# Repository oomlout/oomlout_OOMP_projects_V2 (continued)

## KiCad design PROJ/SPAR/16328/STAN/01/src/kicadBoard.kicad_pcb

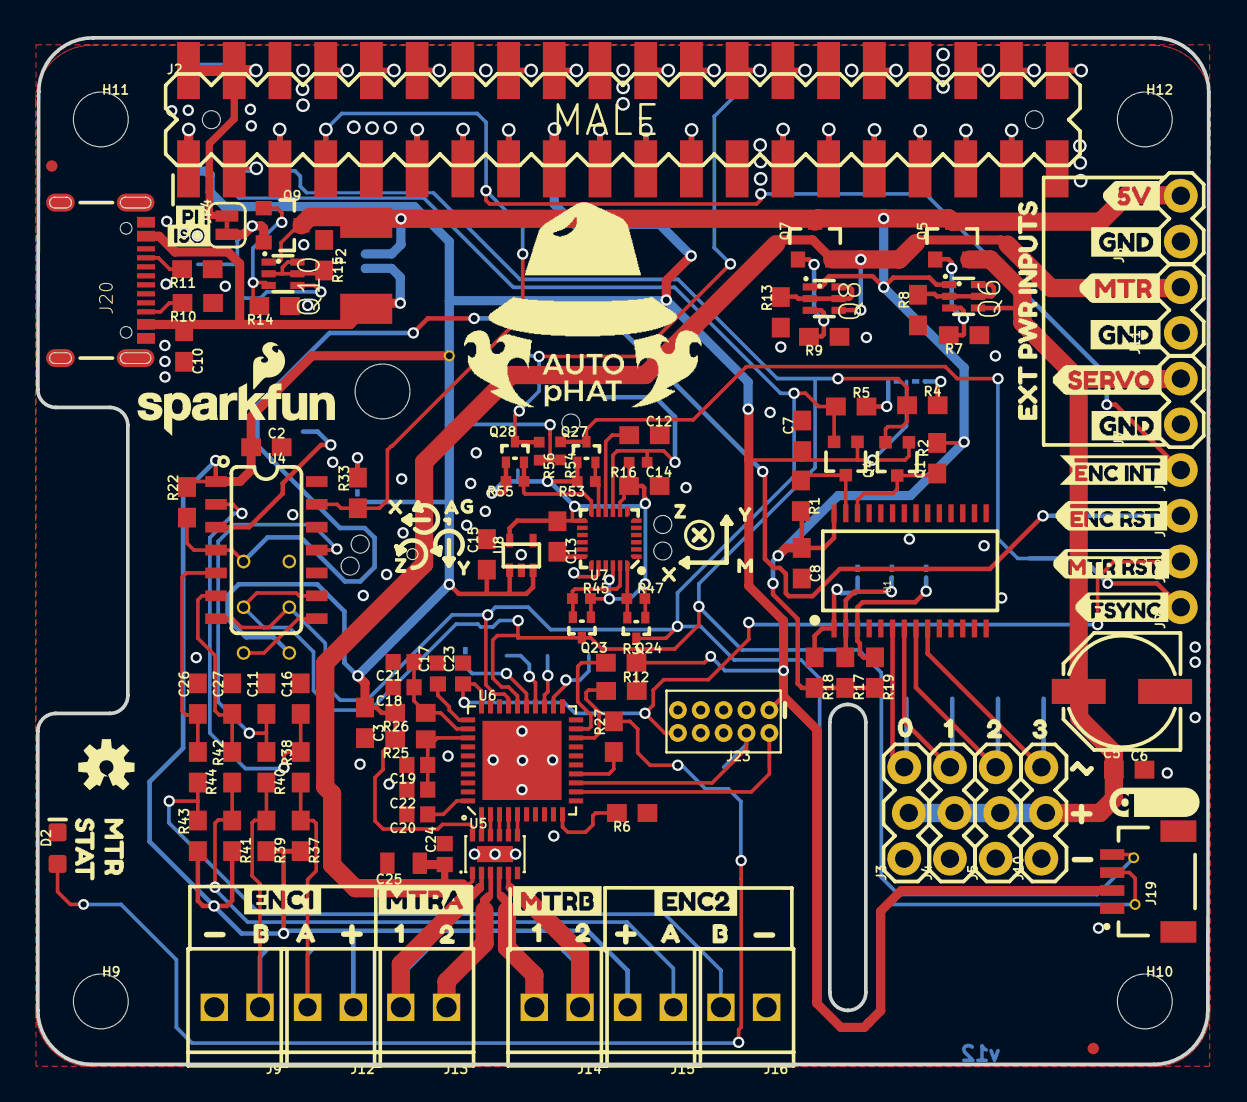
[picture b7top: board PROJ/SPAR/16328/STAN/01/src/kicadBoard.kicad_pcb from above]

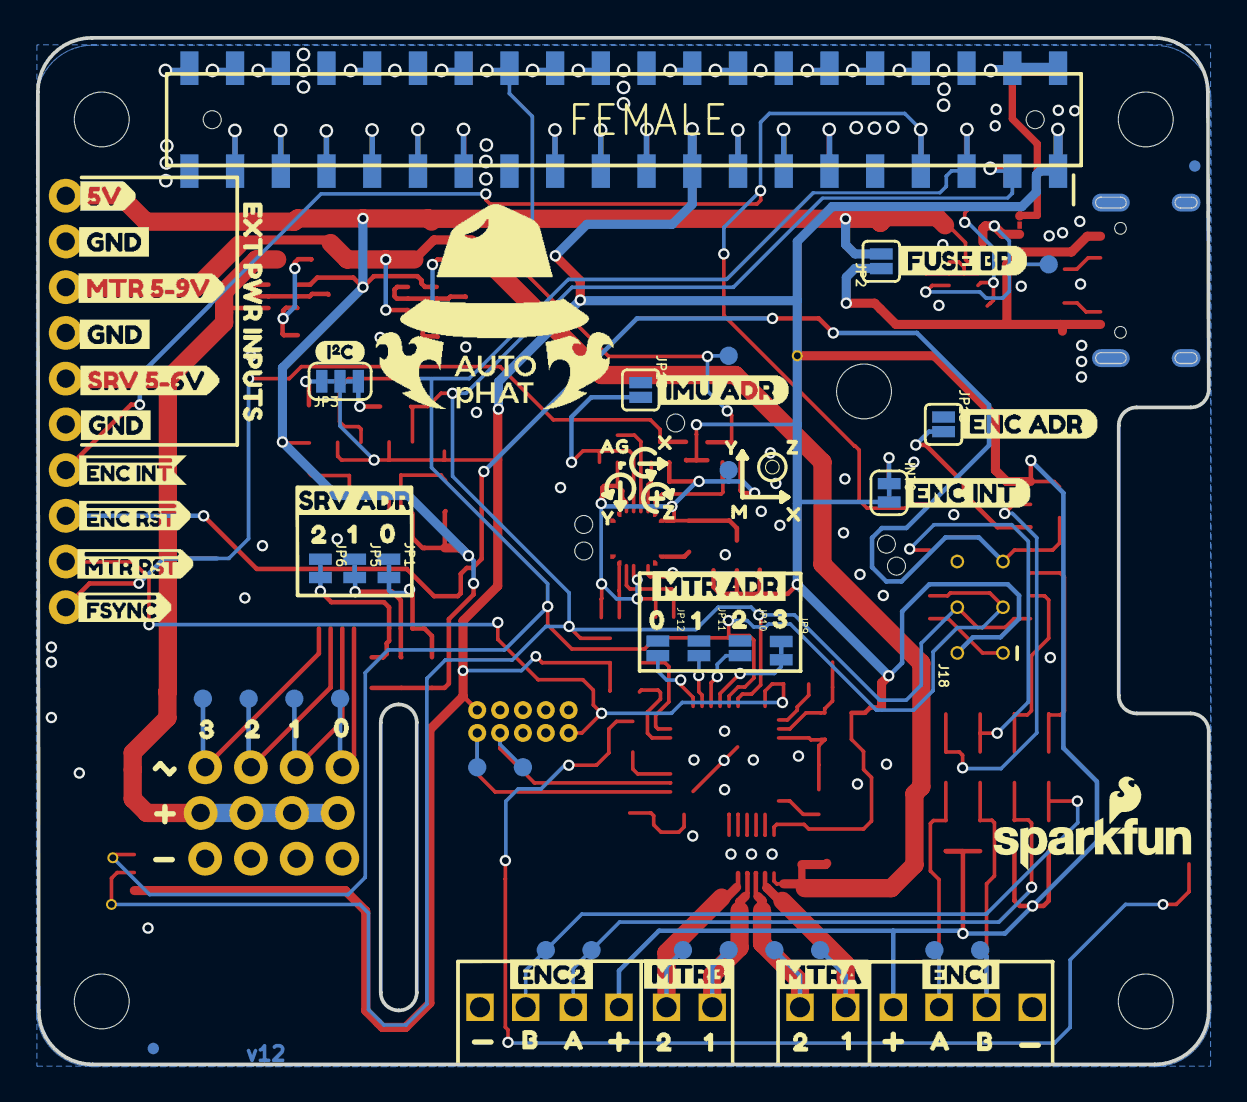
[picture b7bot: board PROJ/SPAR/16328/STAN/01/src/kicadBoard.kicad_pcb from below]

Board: 2 copper layers, 65.1 x 57.0 mm, 252 parts (84 on the bottom side), 100 nets.

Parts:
@HOLE0, @HOLE1, @HOLE2, @HOLE3, @HOLE4, @HOLE5: (no value)
C2, C3, C6, C7, C8, C10, C12, C13: 0.1uF; 0603
C5: 100uF; PANASONIC_D
C11, C16, C26, C27: 10nF; 0603
C14, C15: 1.0uF; 0603
C17, C18, C19, C20: 1.0uF; 0402
C21, C22, C23, C24: 0.1uF; 0402
C25: 10uF; 0805
D2: BLUE; LED-0603@1
F2: 16V/2.5A(5A TRIP); 1812
FD5, FD6, FD7, FD8: FIDUCIALUFIDUCIAL; FIDUCIAL-MICRO
FRAME1: FRAME-LETTERNO_PACKAGE; DUMMY
FRAME2, FRAME3: FRAME-LEDGER; CREATIVE_COMMONS
H9, H10, H11, H12: STAND-OFFTIGHT; STAND-OFF-TIGHT
INT0: SMT-JUMPER_2_NC_TRACE_SILK
J2: RASPBERRYPI-40-PIN-GPIO_SMD_STACKABLE_NOHOLES; RASPBERRY_PI_HAT_40_PIN_SMD_STACKABLE_NOHOLES
J3, J4, J5, J10: 1X03_LOCK
J6, J17, J21, J22: 1X01_NO_SILK
J7: EXT SERVO PWR; 1X02
J8: EXT 5V PWR; 1X02
J9, J13, J14, J16: 1X02_2.54_SCREWTERM_LG_DRILL
J11: EXT MTR PWR; 1X02
J12, J15: 1X02_2.54_SCREWTERM
J18: ISP; 2X3_TEST_POINTS
J19: JST04_1MM_RA
J20: USB C; USB-C-16P
J23: CORTEX_JTAG_DEBUG_PTH; 2X5-PTH-1.27MM
JP1, JP5, JP6, JP9: JUMPER-PAD-2; SMT-JUMPER_2_NC_TRACE_NO-SILK
JP2: FUSE BP; SMT-JUMPER_2_NO_SILK
JP3: I2C; SMT-JUMPER_3_2-NC_TRACE_SILK
JP4: PI ISO; SMT-JUMPER_2_NC_TRACE_SILK
JP10, JP11, JP12: JUMPER-PAD-2; SMT-JUMPER_2_NO_NO-SILK
JP13, JP15: ADR; SMT-JUMPER_2_NO_SILK
LOGO1, LOGO4: SFE_LOGO_NAME_FLAME.1_INCH; SFE_LOGO_NAME_FLAME_.1
LOGO2: OSHW-LOGOS; OSHW-LOGO-S
Q1, Q4: 310mA/60V/1.6Ω; SOT323
Q5, Q7, Q9: 20V/4.2A/52mΩ/1.4W; SOT23-3
Q6, Q8, Q10: SOT363_PHILIPS
Q23, Q24, Q27, Q28: 20V/0.2A/8MHz/1.2Ω/1Vth; SOT-416FL
R1, R2, R4, R5, R8, R13, R15, R17, R18, R19, R22, R33, R37, R38, R39, R40, R41, R42, R43, R44: 10k; 0603@1
R3, R6, R10, R11, R12: 5.1k; 0603@1
R7, R9, R14: 47k; 0603@1
R16, R45, R47, R53, R54, R55, R56: 2.2k; 0402-TIGHT
R25, R26: 1; 0603@1
R27: 470; 0603@1
TP0, TP1, TP2, TP3, TP6, TP7, TP8, TP10, TP11, TP12, TP13, TP14, TP15, TP16, TP17, TP18: PAD.03X.04
TP4, TP5, TP19: TP_15TH
TP9: TEST-POINT3X4; PAD.03X.04
U1: PCA9685; TSSOP-28_4MM
U4: ATTINY84-ARDUINO; SO14
U5: DRV8835; WSON-12
U6: CY8C4245LQI-483; QFN-40
U7: 9DoF IMU; QFN24-3X3
U8: 1.8V/100mA; SC70
U$1: QWIIC_LOGO_5MM; QWIIC_5MM
U$2: I_SUPER2_C-()-03
U$3, U$4, U$5, U$59, U$60, U$61: GND3
U$6, U$7, U$75, U$76: 10
U$8, U$79: 00
U$9: #MTR_RST5
U$10: #FSYNC7
U$11: #ENC_RST4
U$12: #ENC_INT6
U$13, U$52: EXT_PWR_INPUTS3
U$14: 5V2
U$15: MTR1
U$16: SERVO0
U$17, U$82: 11
U$18, U$19: 1X06_2.54_SCREWTERM_PIN_REF
U$20, U$21, U$65, U$66: B15
U$22, U$67: ENC112
U$23, U$68: ENC213
U$24, U$80: 22
U$25, U$81: 33
U$26, U$27, U$69, U$70: A14
U$29: STAT4
U$30: SRV_5#6V1
U$31, U$73: MTRA0
U$32: ISO1
U$33, U$41: 05
U$34, U$42: 16
U$35: PI0
U$36, U$45: 27
U$37: 38
U$38: MTR_5#9V0
U$39: IMU_ADR9
U$40, U$74: MTRB1
U$43, U$44, U$77, U$78: 21
U$46: MTR0
U$47: SRV_ADR0
U$48: ENC_INT12
U$49: ENC_ADR11
U$50: FUSE_BP10
U$51: MTR_ADR0
U$53: 5V3
U$56: #ENC_RST6
U$57: #MTR_RST7
U$58: #FSYNC8
U$62: #ENC_INT0
U$83, U$85: AUTOHAT-LOGO
U$103, U$109, U$123, U$126: X0
U$104, U$110, U$124, U$127: Y1
U$105, U$111, U$125, U$128: Z2
U$106, U$129: G5
U$107, U$130: A4
U$108, U$122: M3

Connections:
1.8V: C13.1, C14.1, Q23.1, Q24.1, Q27.1, Q28.1, R16.2, R45.2, R47.2, R53.2, R55.2, TP9.P$1, U7.8, U7.13, U7.22, U8.5
3.3V: C2.1, C3.1, C7.1, C15.1, INT0.2, J2.1, J2.1B, J2.17, J2.17B, J12.P2, J15.P1, J18.2, J19.2, J23.1, JP3.2, Q1.1, Q4.1, R3.2, R12.2, R22.2, R25.2, R26.2, R37.2, R39.2, R41.2, R43.1, R54.2, R56.2, TP19.P$1, U4.1, U5.12, U8.1, U8.3
5V: C8.1, F2.2, J8.2, JP2.2, Q5.3, Q6.1, Q7.3, Q8.1, Q9.3, Q10.1, R1.2, R2.2, R17.2, R18.2, R19.2, U1.28
AD0/SDO: JP15.2, R16.1, U7.9
ADD_A0: JP1.2, R18.1, U1.1
ADD_A1: JP5.2, R17.1, U1.2
ADD_A2: JP6.2, R19.1, U1.3
ADR: JP13.2, U4.3
AOUT1: J13.P1, TP16.P$1, U5.2
AOUT2: J13.P2, TP15.P$1, U5.3
BOUT1: J14.P1, TP14.P$1, U5.4
BOUT2: J14.P2, TP13.P$1, U5.5
CC1: J20.A5, R11.2
CC2: J20.B5, R10.2
CE0: J2.24, J2.24B
CH0: J3.3, TP0.P$1, U1.6
CH1: J4.3, TP1.P$1, U1.7
CH2: J5.3, TP2.P$1, U1.8
CH3: J10.3, TP3.P$1, U1.9
CONFIG_OUT: R6.2, U6.10
ENC1A_FILTERED: C16.1, R38.2, U4.2
ENC1A_RAW: J12.P1, R37.1, R38.1, TP17.P$1
ENC1B_FILTERED: C11.1, R40.1, U4.11
ENC1B_RAW: J9.P2, R39.1, R40.2, TP18.P$1
ENC2A_FILTERED: C27.1, R42.2, U4.6
ENC2A_RAW: J15.P2, R41.1, R42.1, TP12.P$1
ENC2B_FILTERED: C26.1, R44.1, U4.5
ENC2B_RAW: J16.P1, R43.2, R44.2, TP11.P$1
GND: C2.2, C3.2, C5.-, C6.2, C7.2, C8.2, C10.2, C11.2, C12.2, C13.2, C14.2, C15.2, C16.2, C17.2, C18.2, C19.2, C20.2, C21.2, C22.2, C23.2, C24.2, C25.2, C26.2, C27.2, D2.C, J2.6, J2.6B, J2.9, J2.9B, J2.14, J2.14B, J2.20, J2.20B, J2.25, J2.25B, J2.30, J2.30B, J2.34, J2.34B, J2.39, J2.39B, J3.1, J4.1, J5.1, J7.1, J8.1, J9.P1, J10.1, J11.1, J16.P2, J18.6, J19.1, J20.GND, J20.GND2, J23.3, J23.5, J23.7, J23.9, JP1.1, JP5.1, JP6.1, JP9.1, JP10.1, JP11.1, JP12.1, JP13.1, JP15.1, R6.1, R7.1, R8.1, R9.1, R10.1, R11.1, R13.1, R14.1, R15.1, U1.4, U1.5, U1.14, U1.23, U1.25, U4.14, U5.6, U5.PAD, U6.9, U6.34, U6.EP, U7.18, U7.20, U8.2
GP5: J2.29, J2.29B
GP6: J2.31, J2.31B
GP12: J2.32, J2.32B
GP13: J2.33, J2.33B
GP16: J2.36, J2.36B
GP17: J2.11, J2.11B
GP18: J2.12, J2.12B
GP19: J2.35, J2.35B
GP20: J2.38, J2.38B
GP21: J2.40, J2.40B
GP22: J2.15, J2.15B
GP23: J2.16, J2.16B
GP24: J2.18, J2.18B
GP25: J2.22, J2.22B
GP26: J2.37, J2.37B
GP27: J2.13, J2.13B
ID_SC: J2.28, J2.28B
ID_SD: J2.27, J2.27B
IMU_INT_3.3V: J2.26, J2.26B, Q28.3, R56.1, TP10.P$1
INT_1.8V: Q28.2, R55.1, U7.12
INT_R: INT0.1, R33.2
MISO: J18.1, U4.8
MODEB0: JP12.2, U6.22
MODEB1: JP11.2, U6.23
MODEB2: JP10.2, U6.24
MODEB3: JP9.2, U6.25
unnamed: Q5.1, Q6.3, R7.2
unnamed: JP3.3, R4.2
unnamed: Q1.3, R2.1, U1.26
unnamed: Q4.3, R1.1, U1.27
unnamed: JP3.1, R5.2
unnamed: Q6.2, Q6.5, Q6.6, R8.2
unnamed: Q7.1, Q8.3, R9.2
unnamed: Q8.2, Q8.5, Q8.6, R13.2
unnamed: Q9.1, Q10.3, R14.2
unnamed: Q10.2, Q10.5, Q10.6, R15.2
unnamed: J2.2, J2.2B, J2.4, J2.4B, JP4.2
unnamed: C17.1, U6.31
unnamed: C19.1, C22.1, R25.1, U6.33
unnamed: C20.1, U6.40
unnamed: D2.A, R27.2
unnamed: C12.1, U7.10
P2.0: U5.11, U6.1
P2.1: U5.10, U6.2
P2.2: U5.9, U6.3
P2.3: U5.8, U6.4
P2.4: U5.7, U6.5
P3.2: J23.2, TP7.P$1, U6.12
P3.3: J23.4, TP8.P$1, U6.13
PI-5V: JP4.1, Q9.2, Q10.4, TP6.P$1
PI_MISO: J2.21, J2.21B
PI_MOSI: J2.19, J2.19B
PI_RXI: J2.10, J2.10B
PI_TXO: J2.8, J2.8B
SCLK: J2.23, J2.23B
SCL_1.8V: Q23.2, R45.1, U7.23
SCL_3.3V: J2.5, J2.5B, J18.3, J19.4, Q1.2, Q23.3, R4.1, TP4.P$1, U4.9, U6.26
SCL_OUT: R12.1, U6.18
SDA_1.8V: Q24.2, R47.1, U7.24
SDA_3.3V: J2.3, J2.3B, J18.4, J19.3, Q4.2, Q24.3, R5.1, TP5.P$1, U4.7, U6.27
SDA_OUT: R3.1, U6.19
SERVO: C5.+, C6.1, J3.2, J4.2, J5.2, J7.2, J10.2, Q5.2, Q6.4
SLED: R27.1, U6.14
VBUS: C10.1, F2.1, J20.VBUS1, J20.VBUS2, JP2.1
VDDD1: C18.1, C21.1, R26.1, U6.32
VIN-MTR: C24.1, C25.1, J11.2, Q7.2, Q8.4, U5.1
~ENC_INT: J2.7, J2.7B, J6.1, R33.1, U4.13
~ENC_RST: J17.1, J18.5, R22.1, U4.4
~FSYNC_1.8V: Q27.2, R53.1, U7.11
~FSYNC_3.3V: J21.1, Q27.3, R54.1
~MTR_RST: C23.1, J22.1, J23.10, U6.30

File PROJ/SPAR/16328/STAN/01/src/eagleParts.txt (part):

Partlist

Exported from boardEagle.brd at 20/08/2022 04:54

EAGLE Version 9.6.2 Copyright (c) 1988-2020 Autodesk, Inc.

Assembly variant: 

Part     Value                                         Package                                       Library                      Position (inch)       Orientation

C2       0.1uF                                         0603                                          SparkFun-Capacitors          (0.5 1.35)            R0
C3       0.1uF                                         0603                                          SparkFun-Capacitors          (0.71560002 0.74730007) R270
C5       100uF                                         PANASONIC_D                                   SparkFun-Capacitors          (2.37119993 0.81580007) R180
C6       0.1uF                                         0603                                          SparkFun-Capacitors          (2.38700025 0.64469993) R0
C7       0.1uF                                         0603                                          SparkFun-Capacitors          (1.67179995 1.37489998) R90
C8       0.1uF                                         0603                                          SparkFun-Capacitors          (1.67089998 1.09629983) R270
C10      0.1uF                                         0603                                          SparkFun-Capacitors          (0.32 1.57030007)     R270
C11      10nF                                          0603                                          SparkFun-Capacitors          (0.5 0.8)             R90
C12      0.1uF                                         0603                                          SparkFun-Capacitors          (1.32689998 1.37629995) R0
C13      0.1uF                                         0603                                          SparkFun-Capacitors          (1.1365 1.15470005)   R270
C14      1.0uF                                         0603                                          SparkFun-Capacitors          (1.3265 1.26529995)   R0
C15      1.0uF                                         0603                                          SparkFun-Capacitors          (0.982 1.11560002)    R90
C16      10nF                                          0603                                          SparkFun-Capacitors          (0.575 0.8)           R90
C17      1.0uF                                         0402                                          SparkFun-Capacitors          (0.875 0.855)         R90
C18      1.0uF                                         0402                                          SparkFun-Capacitors          (0.8 0.825)           R180
C19      1.0uF                                         0402                                          SparkFun-Capacitors          (0.83 0.655)          R180
C20      1.0uF                                         0402                                          SparkFun-Capacitors          (0.83 0.547)          R180
C21      0.1uF                                         0402                                          SparkFun-Capacitors          (0.8 0.88)            R180
C22      0.1uF                                         0402                                          SparkFun-Capacitors          (0.83 0.601)          R180
C23      0.1uF                                         0402                                          SparkFun-Capacitors          (0.93 0.855)          R90
C24      0.1uF                                         0402                                          SparkFun-Capacitors          (0.89 0.46)           R90
C25      10uF                                          0805                                          SparkFun-Capacitors          (0.8 0.44)            R180
C26      10nF                                          0603                                          SparkFun-Capacitors          (0.35 0.8)            R90
C27      10nF                                          0603                                          SparkFun-Capacitors          (0.425 0.8)           R90
D2       BLUE                                          LED-0603@1                                    SparkFun-LED                 (0.04319993 0.4730999) R90
F2       16V/2.5A(5A TRIP)                             1812                                          SparkFun-Fuses               (0.71829995 1.74670005) R90
FD5      FIDUCIALUFIDUCIAL                             FIDUCIAL-MICRO                                SparkFun-Aesthetics          (2.30849446 0.03484018) R0
FD6      FIDUCIALUFIDUCIAL                             FIDUCIAL-MICRO                                SparkFun-Aesthetics          (2.30849446 0.03484018) MR0
FD7      FIDUCIALUFIDUCIAL                             FIDUCIAL-MICRO                                SparkFun-Aesthetics          (0.03054011 1.96506373) R0
FD8      FIDUCIALUFIDUCIAL                             FIDUCIAL-MICRO                                SparkFun-Aesthetics          (0.03054011 1.96506373) MR0
INT                                                    SMT-JUMPER_2_NC_TRACE_SILK                    SparkFun-Jumpers             (0.6989001 1.25019993) MR270
J2       RASPBERRYPI-40-PIN-GPIO_SMD_STACKABLE_NOHOLES RASPBERRY_PI_HAT_40_PIN_SMD_STACKABLE_NOHOLES SparkFun-Connectors          (0.3296063 2.01637795) R0
J3                                                     1X03_LOCK                                     SparkFun-Connectors          (1.9 0.45)            R90
J4                                                     1X03_LOCK                                     SparkFun-Connectors          (2 0.45)              R90
J5                                                     1X03_LOCK                                     SparkFun-Connectors          (2.1 0.45)            R90
J6                                                     1X01_NO_SILK                                  SparkFun-Connectors          (2.5 1.3)             R90
J7       EXT SERVO PWR                                 1X02                                          SparkFun-Connectors          (2.5 1.4)             R90
J8       EXT 5V PWR                                    1X02                                          SparkFun-Connectors          (2.5 1.8)             R90
J9                                                     1X02_2.54_SCREWTERM_LG_DRILL                  autophat                     (0.486 0.125)         R180
J10                                                    1X03_LOCK                                     SparkFun-Connectors          (2.2 0.45)            R90
J11      EXT MTR PWR                                   1X02                                          SparkFun-Connectors          (2.5 1.6)             R90
J12                                                    1X02_2.54_SCREWTERM                           SparkFun-Connectors          (0.69 0.125)          R180
J13                                                    1X02_2.54_SCREWTERM_LG_DRILL                  autophat                     (0.894 0.125)         R180
J14                                                    1X02_2.54_SCREWTERM_LG_DRILL                  autophat                     (1.186 0.125)         R180
J15                                                    1X02_2.54_SCREWTERM                           SparkFun-Connectors          (1.39 0.125)          R180
J16                                                    1X02_2.54_SCREWTERM_LG_DRILL                  autophat                     (1.594 0.125)         R180
J17                                                    1X01_NO_SILK                                  SparkFun-Connectors          (2.5 1.2)             R90
J18      ISP                                           2X3_TEST_POINTS                               SparkFun-Connectors          (0.5 1)               MR90
J19                                                    JST04_1MM_RA                                  SparkFun-Connectors          (2.35 0.4)            R90
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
